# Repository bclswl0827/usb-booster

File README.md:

# USB 5V to 12V Boost Converter

This repository contains a simple USB-powered boost converter board that converts a 5V input into a 12V output using an MC34063 switching regulator. The design is intended for low-power applications that need a cheap and compact 12V supply.

## Features

- USB-C input connector
- Boost converter based on the MC34063
- 12V output for external loads
- KiCad project files for schematic, PCB layout, and manufacturing output
- BOM and positional files included for assembly

Although the efficiency is not especially high, the circuit remains inexpensive and practical for simple projects, small peripherals, and other low-power loads.

## Notes

- This board is best suited for low-power applications.
- The converter efficiency is around 85%, so power loss and heat should be considered for higher-current loads.
- Always verify polarity and wiring before powering the circuit.

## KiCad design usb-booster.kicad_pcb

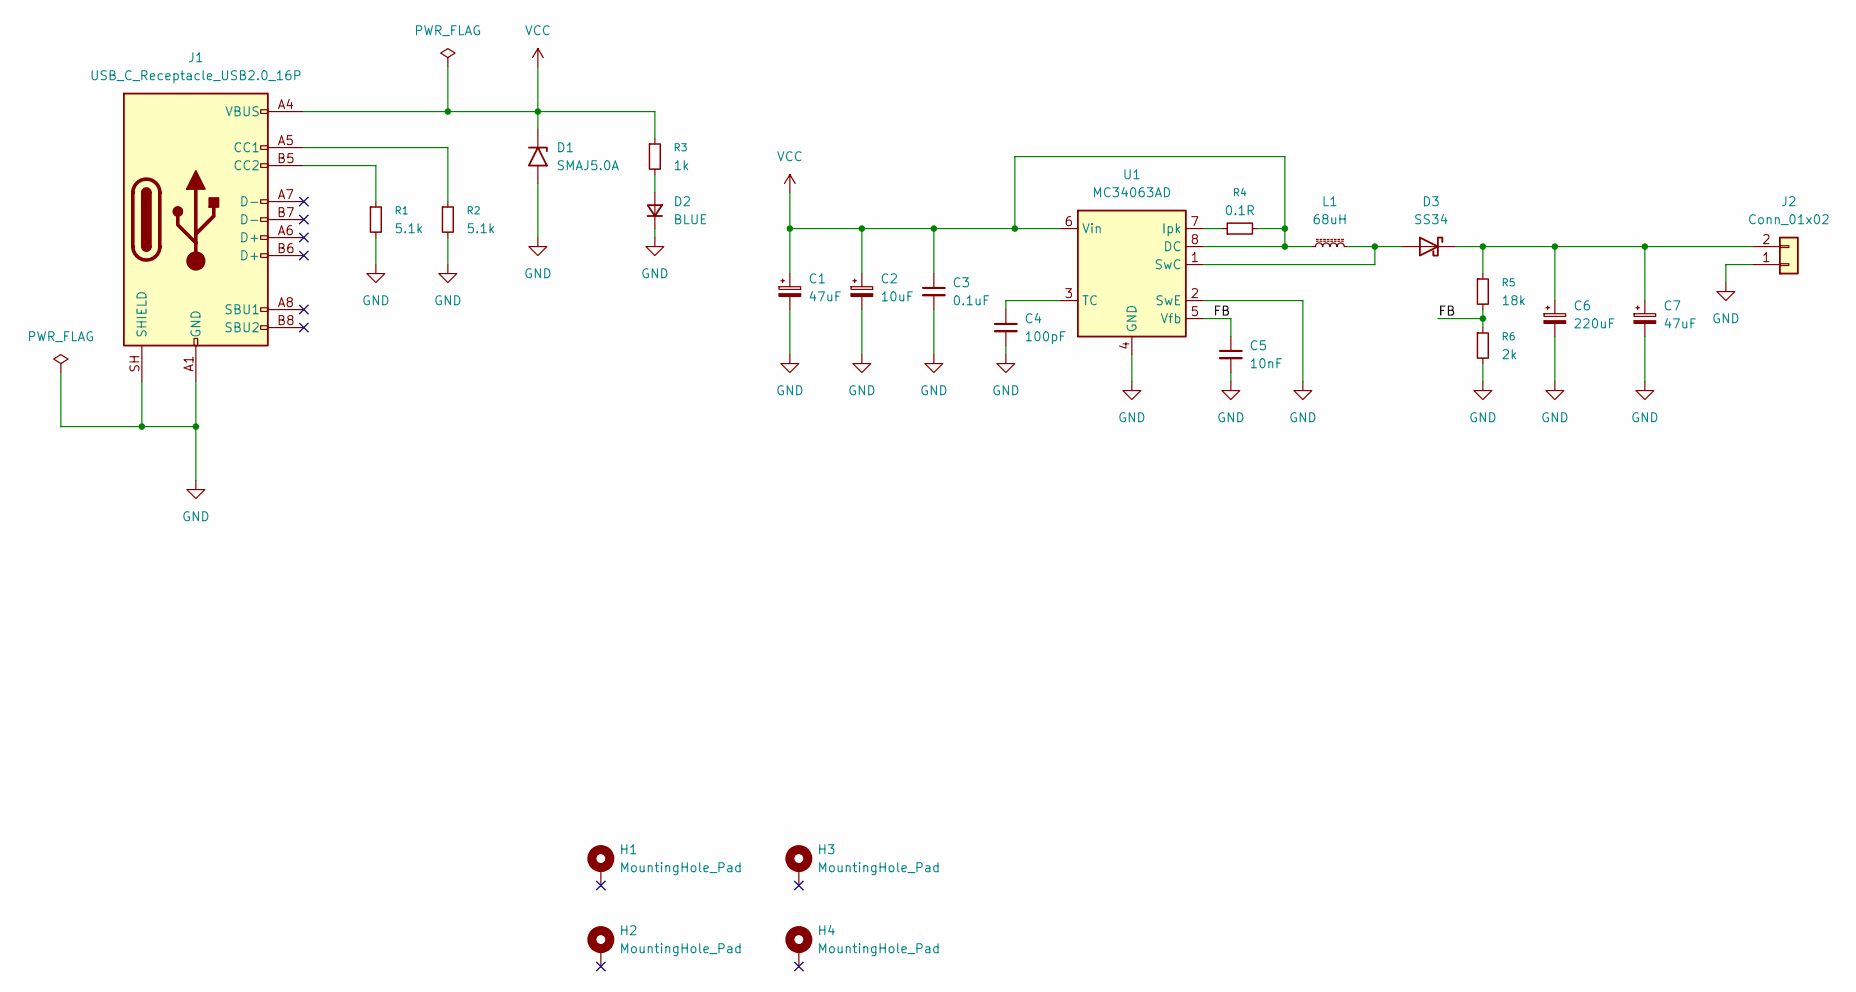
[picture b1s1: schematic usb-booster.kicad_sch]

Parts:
C1: 47uF; CP_EIA-3528-12_Kemet-T
C2: 10uF; CP_EIA-3528-12_Kemet-T
C3: 0.1uF; C_0603_1608Metric
C4: 100pF; C_0603_1608Metric
C5: 10nF; C_0603_1608Metric
C6: 220uF; CP_Elec_6.3x7.7
C7: 47uF; CP_Elec_5x5.4
D1: SMAJ5.0A; D_SMA
D2: BLUE; LED_0603_1608Metric
D3: SS34; D_SMA
H1, H2, H3, H4: MountingHole_Pad; MountingHole_2.2mm_M2_Pad_Via
J1: USB_C_Receptacle_USB2.0_16P; USB_C_Receptacle_GCT_USB4105-xx-A_16P_TopMnt_Horizontal
J2: Conn_01x02; PhoenixContact_MC_1,5_2-G-5.08_1x02_P5.08mm_Horizontal
L1: 68uH; L_Abracon_ASPI-0630LR
R1, R2: 5.1k; R_0603_1608Metric
R3: 1k; R_0603_1608Metric
R4: 0.1R; R_0603_1608Metric
R5: 18k; R_0603_1608Metric
R6: 2k; R_0603_1608Metric
U1: MC34063AD; SOIC-8_3.9x4.9mm_P1.27mm

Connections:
/FB: C5.1, R5.2, R6.1, U1.5 (Vfb)
GND: C1.2, C2.2, C3.2, C4.2, C5.2, C6.2, C7.2, D1.2 (A2), D2.1 (K), J1.A1 (GND), J1.A12 (GND), J1.B1 (GND), J1.B12 (GND), J1.SH (SHIELD), J2.1, R1.2, R2.2, R6.2, U1.2 (SwE), U1.4 (GND)
unnamed: D2.2 (A), R3.2
unnamed: D3.2 (A), L1.2, U1.1 (SwC)
unnamed: C6.1, C7.1, D3.1 (K), J2.2, R5.1
unnamed: J1.A5 (CC1), R2.1
unnamed: J1.B5 (CC2), R1.1
unnamed: R4.1, U1.7 (Ipk)
unnamed: C4.1, U1.3 (TC)
VCC: C1.1, C2.1, C3.1, D1.1 (A1), J1.A4 (VBUS), J1.A9 (VBUS), J1.B4 (VBUS), J1.B9 (VBUS), L1.1, R3.1, R4.2, U1.6 (Vin), U1.8 (DC)

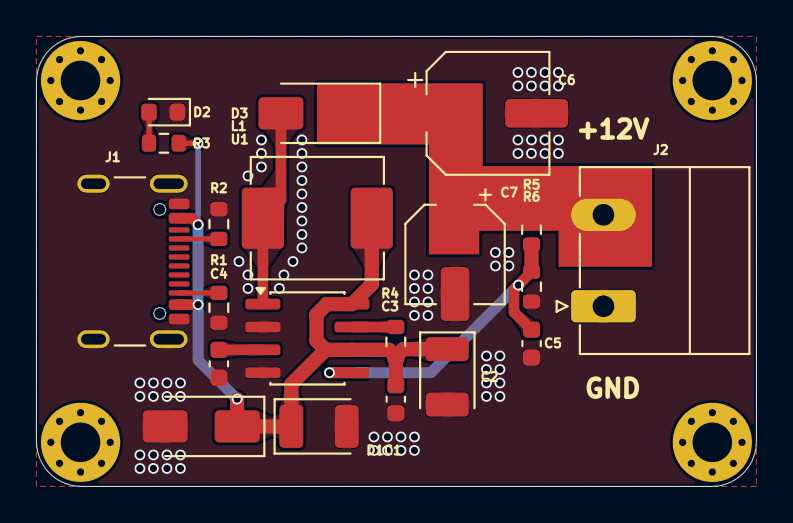
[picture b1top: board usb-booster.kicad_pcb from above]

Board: 2 copper layers, 40.0 x 25.0 mm, 24 parts (0 on the bottom side), 10 nets.
